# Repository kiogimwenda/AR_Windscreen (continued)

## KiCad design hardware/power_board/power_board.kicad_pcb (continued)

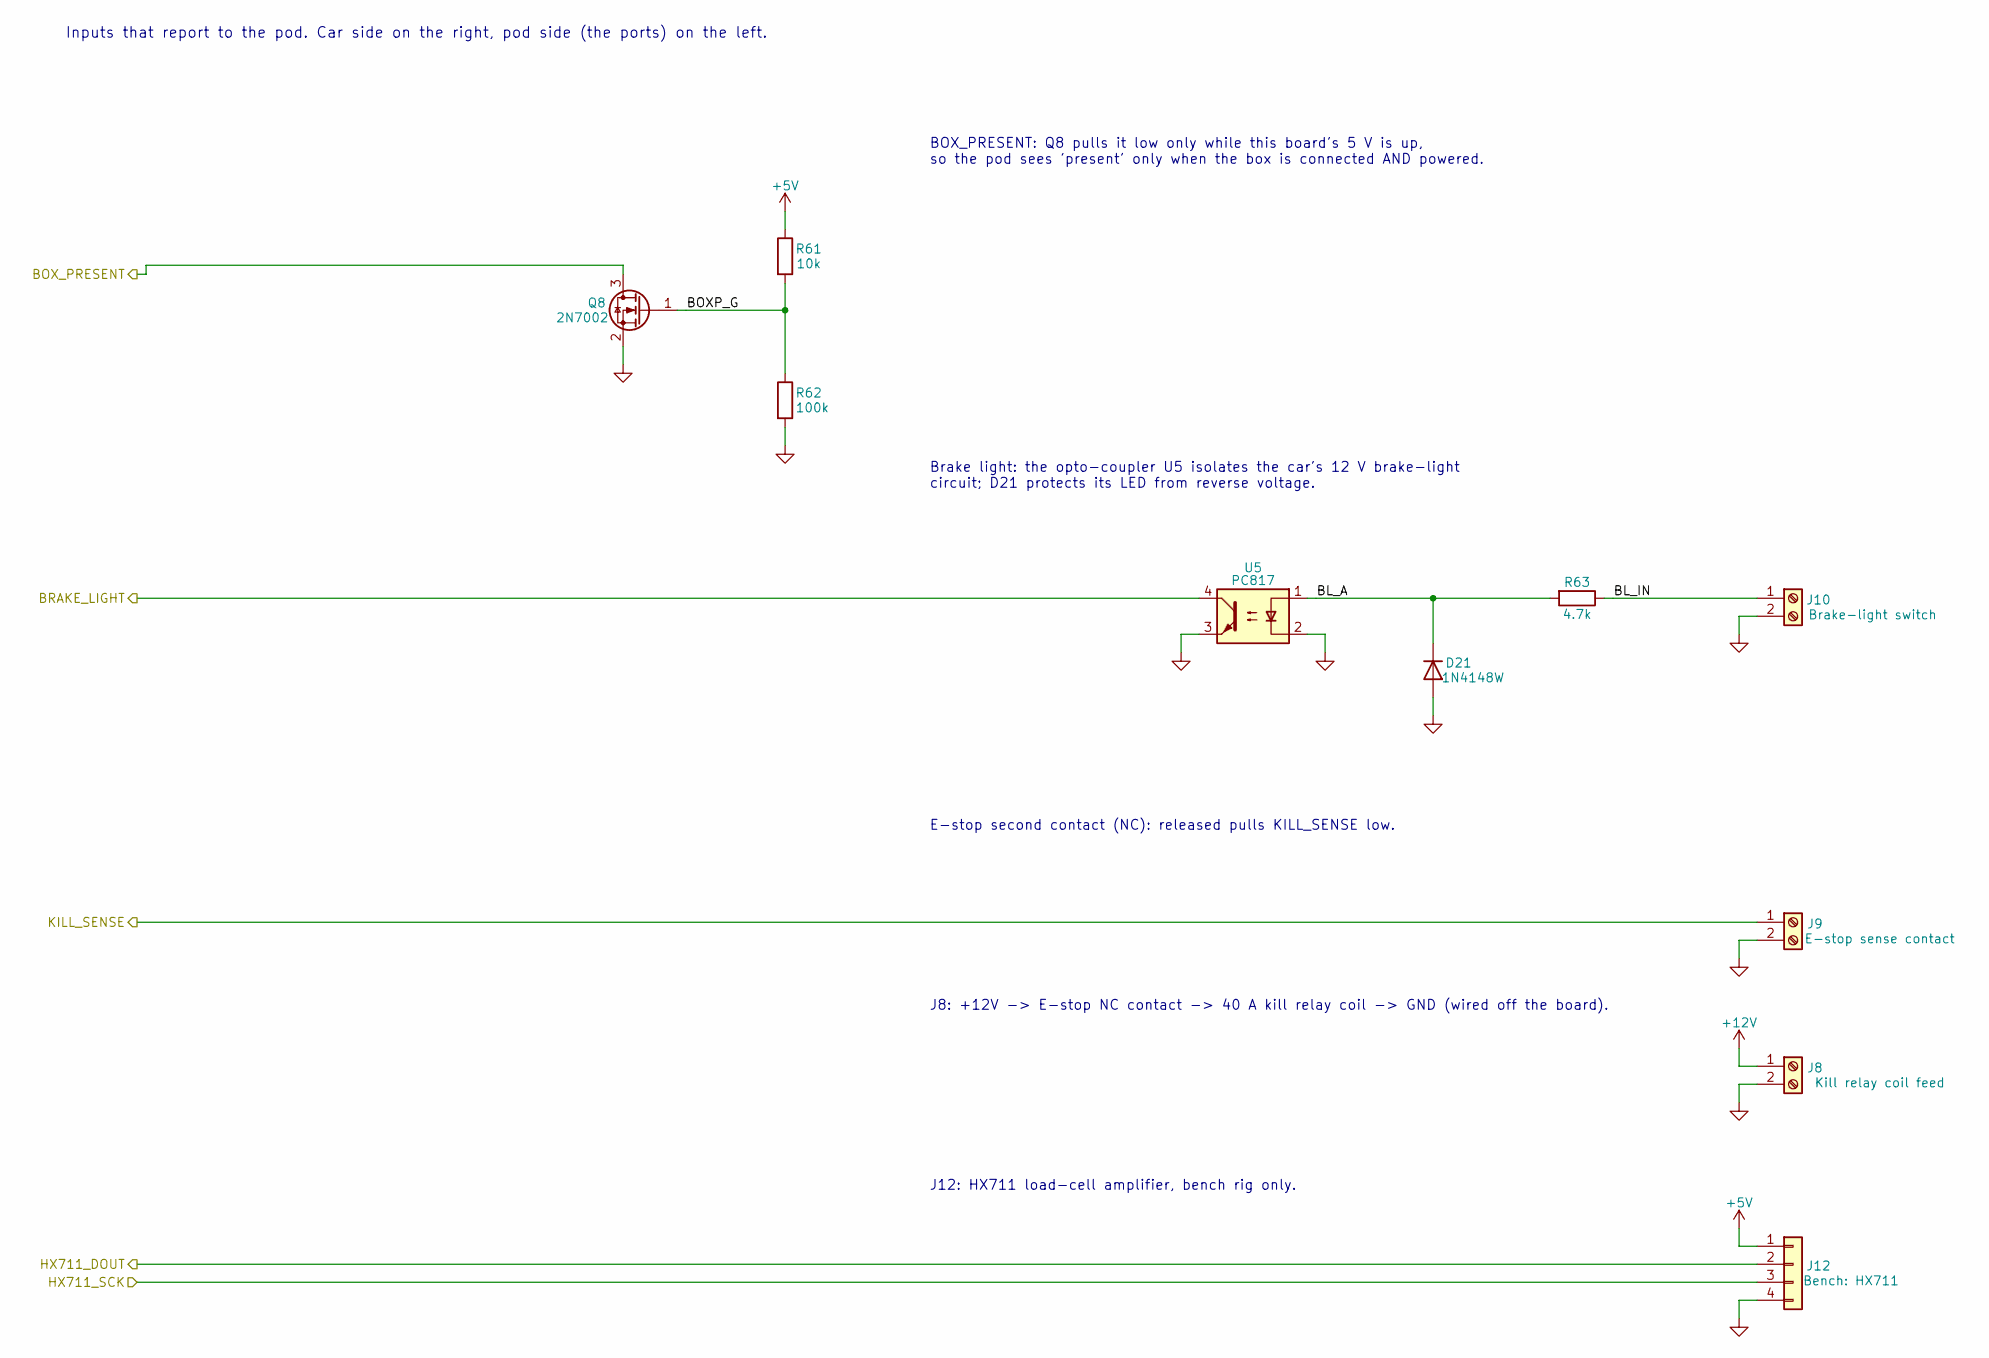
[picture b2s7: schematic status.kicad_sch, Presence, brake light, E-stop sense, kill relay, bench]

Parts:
D21: 1N4148W; D_SOD-123
J8: Kill relay coil feed; TerminalBlock_Phoenix_MKDS-1,5-2-5.08_1x02_P5.08mm_Horizont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
J9: E-stop sense contact; TerminalBlock_Phoenix_MKDS-1,5-2-5.08_1x02_P5.08mm_Horizont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
J10: Brake-light switch; TerminalBlock_Phoenix_MKDS-1,5-2-5.08_1x02_P5.08mm_Horizont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
J12: Bench: HX711; PinHeader_1x04_P2.54mm_Vertical
Q8: 2N7002; SOT-23
R61: 10k; R_0805_2012Metric
R62: 100k; R_0805_2012Metric
R63: 4.7k; R_0805_2012Metric
U5: PC817; DIP-4_W7.62mm

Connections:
+5V: J12.1, R61.1; also elsewhere on the board
+12V: J8.1; also elsewhere on the board
/BOX_PRESENT: Q8.3 (D); also elsewhere on the board
/BRAKE_LIGHT: U5.4; also elsewhere on the board
/HX711_DOUT: J12.2; also elsewhere on the board
/HX711_SCK: J12.3; also elsewhere on the board
/KILL_SENSE: J9.1; also elsewhere on the board
/Presence, brake light, E-stop sense, kill relay, bench/BL_A: D21.1 (K), R63.2, U5.1
/Presence, brake light, E-stop sense, kill relay, bench/BL_IN: J10.1, R63.1
/Presence, brake light, E-stop sense, kill relay, bench/BOXP_G: Q8.1 (G), R61.2, R62.1
GND: D21.2 (A), J8.2, J9.2, J10.2, J12.4, Q8.2 (S), R62.2, U5.2, U5.3; also elsewhere on the board

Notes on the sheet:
Inputs that report to the pod. Car side on the right, pod side (the ports) on the left.
BOX_PRESENT: Q8 pulls it low only while this board's 5 V is up, so the pod sees 'present' only when the box is connected AND powered.
Brake light: the opto-coupler U5 isolates the car's 12 V brake-light circuit; D21 protects its LED from reverse voltage.
E-stop second contact (NC): released pulls KILL_SENSE low.
J8: +12V -> E-stop NC contact -> 40 A kill relay coil -> GND (wired off the board).
J12: HX711 load-cell amplifier, bench rig only.

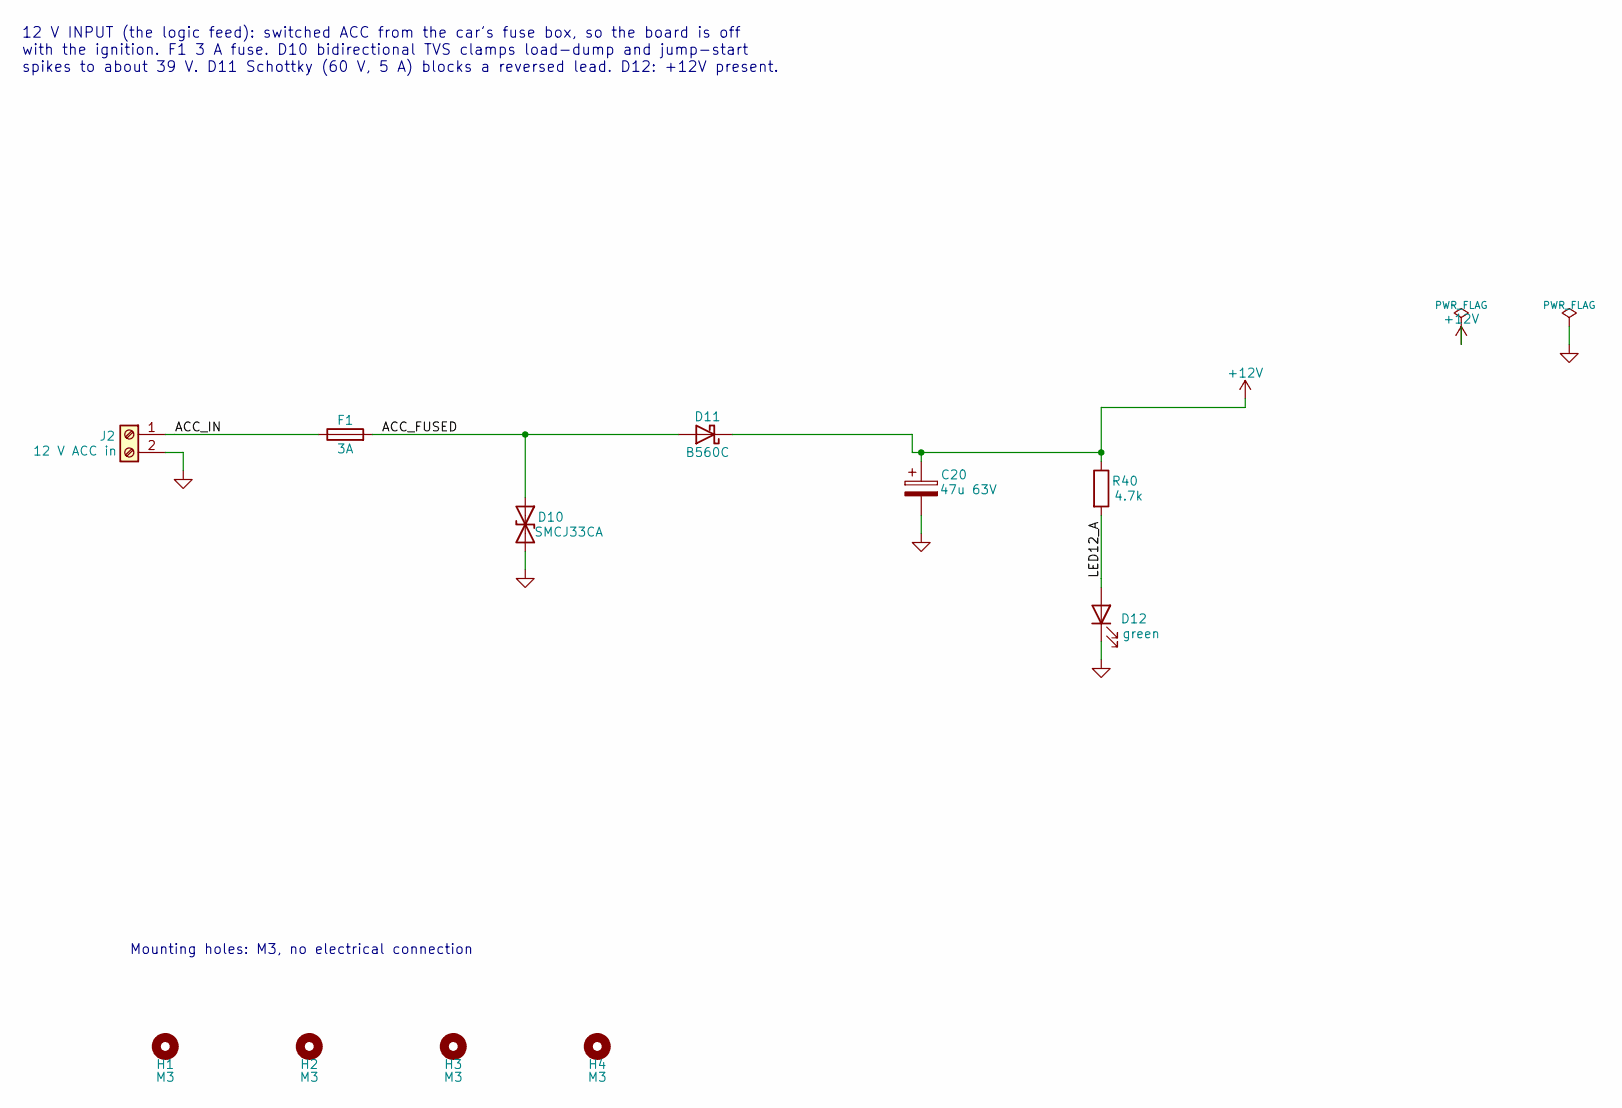
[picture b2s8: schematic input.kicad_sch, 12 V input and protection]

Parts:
C20: 47u 63V; CP_Radial_D8.0mm_P3.50mm
D10: SMCJ33CA; D_SMC
D11: B560C; D_SMC
D12: green; LED_0805_2012Metric
F1: 3A; Fuseholder_Blade_Mini_Keystone_3568
H1, H2, H3, H4: M3; MountingHole_3.2mm_M3
J2: 12 V ACC in; TerminalBlock_Phoenix_MKDS-1,5-2-5.08_1x02_P5.08mm_Horizont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
R40: 4.7k; R_0805_2012Metric

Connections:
+12V: C20.1, D11.1 (K), R40.1; also elsewhere on the board
/12 V input and protection/ACC_FUSED: D10.1 (A1), D11.2 (A), F1.2
/12 V input and protection/ACC_IN: F1.1, J2.1
/12 V input and protection/LED12_A: D12.2 (A), R40.2
GND: C20.2, D10.2 (A2), D12.1 (K), J2.2; also elsewhere on the board

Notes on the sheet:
12 V INPUT (the logic feed): switched ACC from the car's fuse box, so the board is off with the ignition. F1 3 A fuse. D10 bidirectional TVS clamps load-dump and jump-start spikes to about 39 V. D11 Schottky (60 V, 5 A) blocks a reversed lead. D12: +12V present.
Mounting holes: M3, no electrical connection

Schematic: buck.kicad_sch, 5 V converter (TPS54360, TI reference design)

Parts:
C21, C22: 2.2u 100V; C_1210_3225Metric
C23: 100n; C_0805_2012Metric
C24, C25: 47u; C_1210_3225Metric
C26: 6800p; C_0805_2012Metric
C27: 39p; C_0805_2012Metric
D13: B560C; D_SMC
L1: 8.2u; L_Bourns_SRR1260
R41: 523k; R_0805_2012Metric
R42: 84.5k; R_0805_2012Metric
R43: 162k; R_0805_2012Metric
R44: 53.6k; R_0805_2012Metric
R45: 10.2k; R_0805_2012Metric
R46: 13.0k; R_0805_2012Metric
U1: TPS54360DDA; TI_SO-PowerPAD-8_ThermalVias

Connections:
+5V: C24.1, C25.1, L1.2, R44.1; also elsewhere on the board
+12V: C21.1, C22.1, R41.1, U1.2 (VIN); also elsewhere on the board
/5 V converter (TPS54360, TI reference design)/BOOT: C23.1, U1.1 (BOOT)
/5 V converter (TPS54360, TI reference design)/BUCK_COMP: C27.1, R46.1, U1.6 (COMP)
/5 V converter (TPS54360, TI reference design)/BUCK_COMP_RC: C26.1, R46.2
/5 V converter (TPS54360, TI reference design)/BUCK_EN: R41.2, R42.1, U1.3 (EN)
/5 V converter (TPS54360, TI reference design)/BUCK_FB: R44.2, R45.1, U1.5 (FB)
/5 V converter (TPS54360, TI reference design)/BUCK_RT: R43.1, U1.4 (RT/CLK)
/5 V converter (TPS54360, TI reference design)/BUCK_SW: C23.2, D13.1 (K), L1.1, U1.8 (SW)
GND: C21.2, C22.2, C24.2, C25.2, C26.2, C27.2, D13.2 (A), R42.2, R43.2, R45.2, U1.7 (GND), U1.9 (GNDPAD); also elsewhere on the board

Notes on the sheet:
5 V: TI's TPS54360 5 V / 3.5 A reference design (datasheet SLVSBB4G, Figure 34), unchanged. Rated to 60 V input, so whatever the TVS lets through a load dump cannot destroy it. R41/R42 start it at 8 V and stop it at 6.25 V. R43 sets 600 kHz. R44/R45 set 5.0 V. C23 is the bootstrap for the high-side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

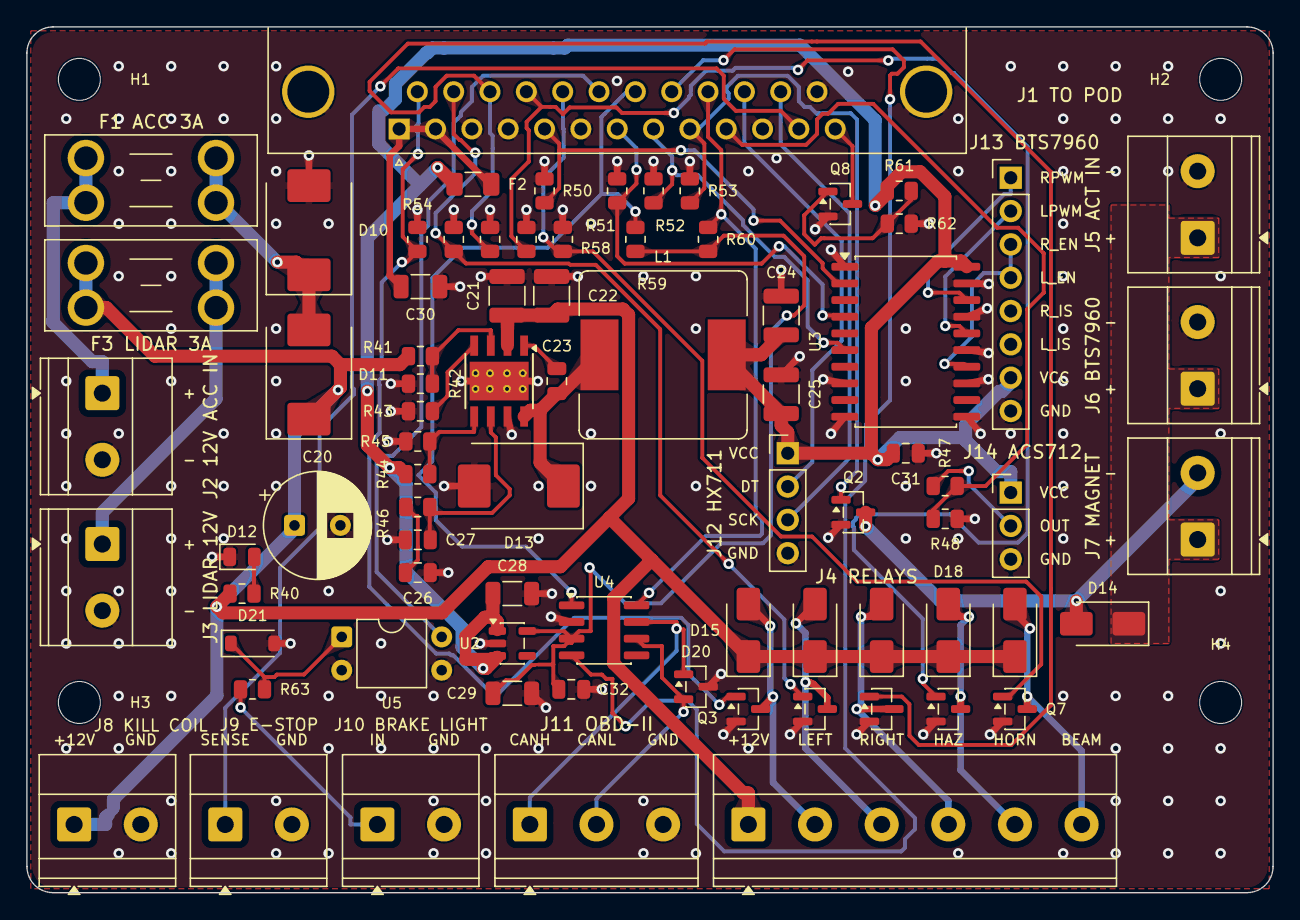
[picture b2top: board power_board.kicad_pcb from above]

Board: 2 copper layers, 95.0 x 66.0 mm, 82 parts (0 on the bottom side), 50 nets.

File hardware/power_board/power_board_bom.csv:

"Reference","Value","Footprint","QUANTITY","Description"
"C20","47u 63V","Capacitor_THT:CP_Radial_D8.0mm_P3.50mm","1","bulk: damps the harness inductance"
"C21,C22","2.2u 100V","Capacitor_SMD:C_1210_3225Metric","2",""
"C23,C31,C32","100n","Capacitor_SMD:C_0805_2012Metric","3",""
"C24,C25","47u","Capacitor_SMD:C_1210_3225Metric","2",""
"C26","6800p","Capacitor_SMD:C_0805_2012Metric","1",""
"C27","39p","Capacitor_SMD:C_0805_2012Metric","1",""
"C28-C30","10u","Capacitor_SMD:C_1206_3216Metric","3",""
"D10","SMCJ33CA","Diode_SMD:D_SMC","1","fast-transient clamp, above the 35 V suppressed load dump (bidirectional: survives reversed leads)"
"D11,D13","B560C","Diode_SMD:D_SMC","2","catch diode,reverse-polarity protection: 60 V, 5 A; ~0.6 V drop, ~1 W at 2 A"
"D12","green","LED_SMD:LED_0805_2012Metric","1",""
"D14-D19","SS14","Diode_SMD:D_SMA","6","flyback"
"D20","NUP2105L","Package_TO_SOT_SMD:SOT-23","1","CAN bus ESD"
"D21","1N4148W","Diode_SMD:D_SOD-123","1","reverse protection for the opto LED"
"F1,F3","3A","Fuse:Fuseholder_Blade_Mini_Keystone_3568","2","LiDAR feed"
"F2","500mA","Fuse:Fuse_1206_3216Metric","1","the pod's supply up the cable"
"H1-H4","M3","MountingHole:MountingHole_3.2mm_M3","4",""
"J1","DB-25 to pod","Connector_Dsub:DSUB-25_Socket_Horizontal_P2.77x2.84mm_EdgePinOffset4.94mm_Housed_MountingHolesOffset4.94mm","1","shield (shell) bonded to ground at this end only"
"J2","12 V ACC in","TerminalBlock_Phoenix:TerminalBlock_Phoenix_MKDS-1,5-2-5.08_1x02_P5.08mm_Horizontal","1","switched ACC (ignition) feed; its own fuse at the car's fuse box too"
"J3","LiDAR 12 V out","TerminalBlock_Phoenix:TerminalBlock_Phoenix_MKDS-1,5-2-5.08_1x02_P5.08mm_Horizontal","1",""
"J4","Relay coils","TerminalBlock_Phoenix:TerminalBlock_Phoenix_MKDS-1,5-6-5.08_1x06_P5.08mm_Horizontal","1","five 12 V automotive relays in sockets; coil common to +12V"
"J5","Actuator 12 V from kill relay","TerminalBlock_Phoenix:TerminalBlock_Phoenix_MKDS-1,5-2-5.08_1x02_P5.08mm_Horizontal","1","the 40 A kill relay's contacts (BOM 3.5); its coil via the E-stop (J8)"
"J6","BTS7960 B+ / B-","TerminalBlock_Phoenix:TerminalBlock_Phoenix_MKDS-1,5-2-5.08_1x02_P5.08mm_Horizontal","1","the module's motor supply, from the kill relay"
"J7","Cable magnet","TerminalBlock_Phoenix:TerminalBlock_Phoenix_MKDS-1,5-2-5.08_1x02_P5.08mm_Horizontal","1","12 V holding magnet; powered only through the kill relay"
"J8","Kill relay coil feed","TerminalBlock_Phoenix:TerminalBlock_Phoenix_MKDS-1,5-2-5.08_1x02_P5.08mm_Horizontal","1","+12V -> E-stop NC contact -> 40 A relay coil -> GND (off-board wiring)"
"J9","E-stop sense contact","TerminalBlock_Phoenix:TerminalBlock_Phoenix_MKDS-1,5-2-5.08_1x02_P5.08mm_Horizontal","1","E-stop second contact block, NC: closed (released) pulls KILL_SENSE low"
"J10","Brake-light switch","TerminalBlock_Phoenix:TerminalBlock_Phoenix_MKDS-1,5-2-5.08_1x02_P5.08mm_Horizontal","1",""
"J11","OBD-II lead","TerminalBlock_Phoenix:TerminalBlock_Phoenix_MKDS-1,5-3-5.08_1x03_P5.08mm_Horizontal","1","J1962 pin 6 CAN_H, pin 14 CAN_L, pins 4/5 ground; ~0.5 m"
"J12","Bench: HX711","Connector_PinHeader_2.54mm:PinHeader_1x04_P2.54mm_Vertical","1","load-cell amplifier on the bench rig only"
"J13","BTS7960 module","Connector_PinHeader_2.54mm:PinHeader_1x08_P2.54mm_Vertical","1","module header: RPWM LPWM R_EN L_EN R_IS L_IS VCC GND (R_EN and L_EN tied)"
"J14","ACS712 module","Connector_PinHeader_2.54mm:PinHeader_1x03_P2.54mm_Vertical","1",""
"L1","8.2u","Inductor_SMD:L_Bourns_SRR1260","1","SRR1260-8R2Y or similar, Isat > 4.5 A"
"Q2-Q7","AO3400A","Package_TO_SOT_SMD:SOT-23","6",""
"Q8","2N7002","Package_TO_SOT_SMD:SOT-23","1",""
"R40,R63","4.7k","Resistor_SMD:R_0805_2012Metric","2","~2.3 mA LED current at 12 V; 4.7k keeps a 24 V jump-start within 0805"
"R41","523k","Resistor_SMD:R_0805_2012Metric","1","UVLO: start 8 V"
"R42","84.5k","Resistor_SMD:R_0805_2012Metric","1","UVLO: stop 6.25 V"
"R43","162k","Resistor_SMD:R_0805_2012Metric","1","600 kHz"
"R44","53.6k","Resistor_SMD:R_0805_2012Metric","1",""
"R45","10.2k","Resistor_SMD:R_0805_2012Metric","1",""
"R46","13.0k","Resistor_SMD:R_0805_2012Metric","1",""
"R47,R50-R61","10k","Resistor_SMD:R_0805_2012Metric","13","fail-safe: off when not driven,present = connected AND powered,recessive when not driven,standby (cannot transmit) when not driven,x2/3 divider: nothing above 3.3 V on the cable"
"R48","20k","Resistor_SMD:R_0805_2012Metric","1",""
"R62","100k","Resistor_SMD:R_0805_2012Metric","1",""
"U1","TPS54360DDA","Package_SO:TI_SO-PowerPAD-8_ThermalVias","1","60 V, 3.5 A buck"
"U2","AP2112K-3.3","Package_TO_SOT_SMD:SOT-23-5","1","3.3 V for the CAN transceiver"
"U3","74HCT244","Package_SO:SOIC-20W_7.5x12.8mm_P1.27mm","1","TTL-threshold buffer: 3.3 V logic in, 5 V out to the BTS7960 module"
"U4","SN65HVD230","Package_SO:SOIC-8_3.9x4.9mm_P1.27mm","1","beside the OBD lead: the stub on the car's bus is the lead only. No termination."
"U5","PC817","Package_DIP:DIP-4_W7.62mm","1",""

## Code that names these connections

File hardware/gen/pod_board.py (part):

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# push into an unpowered power box (~3 mA, Part 4.8.4), while keeping 20 kHz PWM edges clean
# over 2 m of cable. CAN_TX carries 500 kbit/s: 330 ohm keeps its edges fast.
OUTPUTS = {  # signal: (DB-25 pin, MCU pin number on LQFP64, series ohms)
    "BRAKE_RPWM": (5, "41", "1k"),     # PA8
    "BRAKE_LPWM": (7, "37", "1k"),     # PC6
    "BRAKE_EN": (8, "33", "1k"),       # PB12
    "MAGNET_EN": (9, "35", "1k"),      # PB14
    "RELAY_LEFT": (14, "26", "1k"),    # PB0
    "RELAY_RIGHT": (15, "27", "1k"),   # PB1
    "RELAY_HAZARD": (16, "9", "1k"),   # PC1
    "RELAY_HORN": (17, "10", "1k"),    # PC2
    "RELAY_BEAM": (18, "11", "1k"),    # PC3
    "CAN_TX": (20, "62", "330"),       # PB9
    "CAN_STBY": (22, "53", "1k"),      # PC12
    "HX711_SCK": (24, "20", "1k"),     # PA4
}
# Cable signals read by the pod: 10 k pull-up on the cable side (fail-safe reading when the
# cable is out), then 1 k + 10 nF into the pin (a 10 us filter against PWM crosstalk). CAN_RX and
# HX711_DOUT are data: series resistor only, no capacitor.
INPUTS = {  # signal: (DB-25 pin, MCU pin, pull-up?, filter capacitor?)
    "KILL_SENSE": (12, "36", True, True),      # PB15, NC to ground at the box: open = engaged
    "BOX_PRESENT": (13, "8", True, True),      # PC0, pulled low by the box while powered
    "BRAKE_LIGHT": (19, "57", True, True),     # PB5, optocoupler: low = pedal pressed
    "CAN_RX": (21, "61", True, False),         # PB8, recessive (high) when the cable is out
    "HX711_DOUT": (23, "15", False, False),    # PA1
}

parts = []
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    # USB, SWD
    "44": "USB_DM", "45": "USB_DP", "46": "SWDIO", "49": "SWCLK",
    # on-board sensors and buses
    "59": "IMU_SDA", "58": "IMU_SCL", "24": "IMU_INT", "25": "IMU_RST",     # PB7 PB6 PC4 PC5
    "30": "GEST_SDA", "29": "GEST_SCL", "38": "GEST_INT",                   # PB11 PB10 PC7
    "16": "GPS_TX", "17": "GPS_RX", "56": "GPS_PPS",                        # PA2 PA3 PB4
    "51": "OBD_TX", "52": "OBD_RX",                                         # PC10 PC11 (ELM327)
    "2": "LED_LINK", "39": "LED_ARMED", "40": "LED_FAULT",                  # PC13 PC8 PC9
    "14": "BRAKE_CURRENT",                                                  # PA0
}
for sig, (_, pin, _) in OUTPUTS.items():
    mcu_nets[pin] = sig
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
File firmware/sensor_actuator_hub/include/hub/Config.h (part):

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//
// Pins are chosen from the F405's peripheral map (STM32duino variant F405RGT_F415RGT) and are the
// PCB's netlist: change one here, change the schematic. Drivers take their pins from here and
// never hard-code them. Kept free on purpose: PA13/PA14 (SWD), PA11/PA12 (USB), PH0/PH1 (8 MHz
// crystal), PB2 (BOOT1), PC14/PC15 (no LSE fitted).
// ---------------------------------------------------------------------------------------------

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// --- Pins (Arduino-STM32 names) -----------------------------------------------------------------
// Brake actuator (power box), BTS7960 half-bridges. RPWM drives the actuator in the PULL direction
// (applying the brake through the pull-only cable); LPWM would drive it back and is only ever held
// low. R_EN and L_EN are tied together on the power board: one enable line. PA8 = TIM1_CH1.
#define HUB_PIN_BRAKE_RPWM PA8
#define HUB_PIN_BRAKE_LPWM PC6
#define HUB_PIN_BRAKE_EN PB12
// Actuator current: the ACS712-20A on the power board, its output divided x2/3 THERE (so nothing
// above 3.3 V ever travels up the cable), into ADC1 channel 0.
#define HUB_PIN_BRAKE_CURRENT PA0
// Fail-safe cable release (BOM note B, subject to the actuator design being approved): the 12 V
// holding electromagnet's MOSFET on the power board, powered through the kill relay. LOW = the
// cable drops free.
#define HUB_PIN_CABLE_MAGNET PB14
// Kill-switch SENSE: the E-stop's second contact block, NC to ground at the power box
// (INPUT_PULLUP here). Read-only: the E-stop cuts actuator power in hardware.
#define HUB_PIN_KILL_SENSE PB15
// Power-box presence: pulled LOW inside the power box by a small MOSFET whose gate is fed from the
// box's own 5 V rail, pulled up here. LOW = the cable is in AND the box is powered (the ignition is
// on). Unplugged, broken, or box unpowered: HIGH = absent. An unplugged cable is also seen by the
// kill sense opening: two independent indications.
#define HUB_PIN_BOX_PRESENT PC0
// Signal relays on the power board (automotive relays, low-side MOSFETs, ACTIVE-HIGH): left, right
// indicators; hazards; horn; high beam.
#define HUB_PIN_RELAY_LEFT PB0
#define HUB_PIN_RELAY_RIGHT PB1
#define HUB_PIN_RELAY_HAZARD PC1
#define HUB_PIN_RELAY_HORN PC2
#define HUB_PIN_RELAY_BEAM PC3
// Brake-light switch via the power board's PC817 optocoupler (BOM note C): LOW = pedal pressed.
#define HUB_PIN_BRAKE_LIGHT_SENSE PB5
// Bench rig only: HX711 load-cell amplifier, reached through the cable's two bench conductors.
#define HUB_PIN_HX711_DOUT PA1
#define HUB_PIN_HX711_SCK PA4
// OBD-II over the vehicle's own CAN bus (ISO 15765-4), replacing the ELM327 + HC-05 pair:
//   CAN1 PB8 RX, PB9 TX, as 3.3 V logic down the inter-box cable to an SN65HVD230 transceiver on
//   the POWER board, beside the OBD-II cable (J1962 pins 6 CAN_H, 14 CAN_L). The transceiver sits
//   there, not in the pod, so the unterminated branch this hub adds to the car's bus is the short
//   OBD lead (~0.5 m), not 2.5 m of cable: a long stub reflects on a 500 kbit/s bus.
//   Its Rs pin is pulled HIGH on the power board (standby: driver off, receiver listening), and
//   its D input pulled HIGH (recessive). The firmware drives Rs LOW only while it may transmit.
//   Cable out, pod in reset or unpowered: the transceiver cannot drive the car's bus.
#define HUB_CAN1_RX PB8
#define HUB_CAN1_TX PB9
#define HUB_PIN_CAN_SILENT PC12
// Fallback for pre-CAN vehicles (Part 4.8.5): an ELM327 on USART3 at PC10 TX / PC11 RX, selected
// with -DHUB_OBD_ELM327. Only one OBD driver is ever built.
#define HUB_OBD_TX PC10
#define HUB_OBD_RX PC11
// Buses on the pod board:
//   I2C1   PB6 SCL, PB7 SDA      BNO085 IMU, on the pod board next to the camera
//   I2C2   PB10 SCL, PB11 SDA    APDS-9960 gesture puck, on its own cable (~1.5 m, 100 kHz): its
//                                own bus, so a cable fault cannot hang the IMU
//   USART2 PA2 TX, PA3 RX        u-blox NEO-M8N (antenna on the pod's top face, or a roof antenna)
//   USB    PA11, PA12            USB-CDC to the host (the Part 3 protocol)
#define HUB_IMU_SDA PB7
#define HUB_IMU_SCL PB6
#define HUB_GESTURE_SDA PB11
#define HUB_GESTURE_SCL PB10
#define HUB_GPS_TX PA2
#define HUB_GPS_RX PA3
// Routed on the pod board for later use; no firmware reads them yet (the drivers poll):
// BNO085 interrupt and reset, APDS-9960 interrupt, GNSS one-pulse-per-second.
#define HUB_PIN_IMU_INT PC4
#define HUB_PIN_IMU_RST PC5
#define HUB_PIN_GESTURE_INT PC7
#define HUB_PIN_GPS_PPS PB4
// Status LEDs on the pod's driver-facing edge (active-high): host link, armed, fault.
#define HUB_PIN_LED_LINK PC13
#define HUB_PIN_LED_ARMED PC8
#define HUB_PIN_LED_FAULT PC9

// --- Clock
// ---------------------------------------------------------------------------------------- USB full
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
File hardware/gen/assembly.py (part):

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        notes.append(f"read on MCU pin {mcu}" + ("; 10 k pull-up to 3.3 V" if pull else "")
                     + ("; 1 k + 10 nF filter" if cap else ""))
    elif sig == "BRAKE_CURRENT":
        notes.append("read on MCU pin 14 (PA0) through 1 k + 100 nF; 100 k to GND")
    elif sig == "5V_CABLE":
        notes.append("into VIN_POD through D2 (diode-OR with USB's VBUS through D1)")
    elif sig == "GND":
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        "BRAKE_CURRENT": f"ACS712 output x{DIV:.3f} (R47/R48)",
        "KILL_SENSE": "E-stop second contact (J9), NC to ground",
        "BOX_PRESENT": "Q8 (2N7002) to ground while the box's 5 V is up",
        "BRAKE_LIGHT": "PC817 (U5) output: low = pedal pressed",
        "CAN_RX": "SN65HVD230 (U4) R output",
        "HX711_DOUT": "bench header J12 only",
        "HX711_SCK": "bench header J12 only",
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| +5V | C24 + | **{V5:.2f} V** (0.8 V reference x (1 + {PWR['R44']['value']}/{PWR['R45']['value']})), within 2 % |
| +3V3 | C29 + | 3.30 V (AP2112K-3.3) |
| 5V_POD | DB-25 pin 1 | as +5V |
| LIDAR_12V | J3 pin 1 | as +12V (through F3) |

**Under-voltage lockout** (R41/R42): lower the supply slowly: +5V collapses near **{uvlo_stop}**; raise
it: +5V returns near **{uvlo_start}**. A car's cranking dip must not brown the board out half-way.
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
| Check | Measure | Expect |
|---|---|---|
| BTS7960 inputs off | J13 pins 1-3 (RPWM_5V, LPWM_5V, EN_5V) to GND | 0 V |
| Relays off | Q3-Q7 drains (J4 pins 2-6) | 12 V (coils not pulled down) |
| Magnet off | Q2 drain (J7 pin 2, MAG_NEG) | no voltage across J7 |
| CAN silent | U4 pin 8 (Rs) and pin 1 (D) | 3.3 V: standby, recessive |
| Present | DB-25 pin 13, with the 3.3 V source through 10 kΩ on it; supply on / off | near 0 V (Q8 on) / 3.3 V |
| Current sense idle | DB-25 pin 10 to GND, ACS712 module fitted | **{ACS_IDLE_BOX:.2f} V** (2.5 V zero-current output x{DIV:.3f}) |
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|---|---|---|
| 14-18 | RELAY_LEFT .. RELAY_BEAM | that relay clicks (fit the relays in their sockets first); the others stay off |
| 9 | MAGNET_EN | 12 V across J7 (an LED + resistor stands in for the magnet) |
| 8 | BRAKE_EN | J13 pin 3 rises to ~5 V |
| 5 | BRAKE_RPWM | J13 pin 1 rises to ~5 V |
| 7 | BRAKE_LPWM | J13 pin 2 rises to ~5 V (**never** used in the car: the drive is one-directional) |
| 22 | CAN_STBY pulled LOW instead (through 1 kΩ to GND) | U4 pin 8 goes low: the transceiver is enabled |

Release each: it returns to off by itself. That is the property the whole split rests on.

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   travels up the cable on pins 23/24.
3. **Pod** on USB to the laptop, running the bench build: `pio run -e bench -t upload`.
4. **E-stop** wired and within reach of the person at the pedal.
5. **Oscilloscope** (once, recommended) on J13 pin 3 (EN_5V): the independent timing of item 5.
6. Before the first sweep: `log_actuator_bench.py selftest`, then `status` shows the load cell
   valid and the hub armed only when expected.
7. Run `log_actuator_bench.py checklist --attempt N` three times on three separate occasions (Part
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
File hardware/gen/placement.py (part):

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    "U1": (*MCU, 0, "STM32F405 in the middle: every subsystem fans out to it"),
    "C3": (26.2, 7.7, 0, "100 nF at VDD pin 64 / VSS 63 (top-left pins)"),
    "C4": (36.6, 12.5, 90, "100 nF at VDD pin 48 (right side)"),
    "C11": (36.6, 16.3, 90, "2.2 uF at VCAP2, pin 47: right at the pin"),
    "C7": (39.7, 16.5, 90, "4.7 uF bulk beside the MCU"),
    "C5": (23.9, 24.6, 90, "100 nF at VDD pin 19 / VSS 18 (bottom-left pins)"),
    "C10": (32.0, 25.6, 90, "2.2 uF at VCAP1, pin 31: right at the pin"),
    "C6": (34.3, 25.6, 90, "100 nF at VDD pin 32"),
    "C8": (15.6, 23.6, 90, "1 uF on VDDA, pin 13"),
    "C9": (19.0, 23.3, 0, "100 nF on VDDA, pin 13: the smaller capacitor nearer the pin"),
    # Clock, reset, boot
    "Y1": (17.6, 14.3, 90, "8 MHz crystal, upright, within 5 mm of OSC_IN/OUT (pins 5, 6); nothing routed under it"),
    "C12": (13.0, 18.55, 90, "crystal load capacitor beside Y1 pin 1"),
    "C13": (13.0, 10.05, 90, "crystal load capacitor beside Y1 pin 2"),
    # RESET and BOOT: side-push switches, plungers flush with the left edge, under the SWD header:
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    "F2": (34.0, 12.0, 0, "500 mA polyfuse for the pod's supply, near DB-25 pins 1-2"),
    "C30": (30.0, 19.8, 0, "5V_POD capacitor after the polyfuse"),
    # Presence detector near DB-25 pin 13
    "Q8": (62.0, 13.5, 0, "BOX_PRESENT MOSFET near DB-25 pin 13"),
    "R61": (66.5, 12.5, 0, "presence gate divider (top)"), "R62": (66.5, 15.0, 0, "presence gate divider (bottom)"),
    # Brake actuator side (right): terminals on the right edge, module headers inboard
    "J5": (*right_t(11.0, 2), 90, "actuator 12 V from the kill relay: right edge, the 10 A path starts here"),
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    # CAN above the OBD terminal: the transceiver beside the lead (short stub)
    "U4": (44.0, 46.0, 0, "SN65HVD230 right above the OBD terminal: the bus stub is the lead only"),
    "D20": (51.0, 50.3, 0, "CAN ESD diode between the transceiver and the terminal"),
    "C32": (41.5, 50.5, 0, "transceiver decoupling, beside its VCC pin 3 (the right side stays clear for the CAN_STBY line to pin 8)"),
    "U2": (37.0, 47.0, 0, "3.3 V LDO for the transceiver"),
    "C28": (37.0, 43.2, 0, "LDO input capacitor"), "C29": (37.0, 50.8, 0, "LDO output capacitor"),
}
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# pins (by pad number) are named in line with each pin; both go beside the part's courtyard on
# `side` ("N", "S", "E" or "W": the inboard side for edge parts), unless `at` = (x, y, rotation)
# places the title. Header pins carry the MODULE's pin names, so a breakout plugs in by matching
# names (GNSS TX goes to the MCU's GPS_RX). Text: titles 1.0 mm, pin names 0.8 mm.


def L(title, pins=None, side="E", at=None, ref=True, size=1.0, shift=(0.0, 0.0)):
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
